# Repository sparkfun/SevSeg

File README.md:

This library allows an Arduino to easily display numbers and characters on a 4 digit 7-segment display without a separate 7-segment display controller.
It works for any digital pin arrangement, common anode and common cathode displays. It also has character support including letters A-F and many symbols. 

Hardware Setup
--------------
4 digit 7 segment displays use 12 digital pins. You may need more pins if your display has colons or apostrophes.

There are 4 digit pins and 8 segment pins. Digit pins are connected to the cathodes for common cathode displays, or anodes for common anode displays. 8 pins control the individual segments (seven segments plus the decimal point). 

Connect the four digit pins with four limiting resistors in series to any digital or analog pins. Connect the eight segment pins to any digital or analog pins (no limiting resistors needed). See the SevSeg example for more connection information.

Repository Contents
-------------------

* **/examples** - Arduino example sketches
* **/src** - Source files for Arduino library

Documentation
--------------
* **[Hookup Guide](https://learn.sparkfun.com/tutorials/using-the-serial-7-segment-display)** - Basic hookup guide for the Serial Segment Displays.
* **[Compatible Displays](https://www.sparkfun.com/wish_lists/120699)** - Products that work with this code. 

License Information
-------------------
Original Library by Dean Reading (deanreading@hotmail.com: http://arduino.cc/playground/Main/SevenSegmentLibrary), 2012

Improvements by Nathan Seidle, 2012

All code is open source so please feel free to do anything you want with it; you buy me a beer if you use this and we meet someday ([Beerware license](http://en.wikipedia.org/wiki/Beerware)).

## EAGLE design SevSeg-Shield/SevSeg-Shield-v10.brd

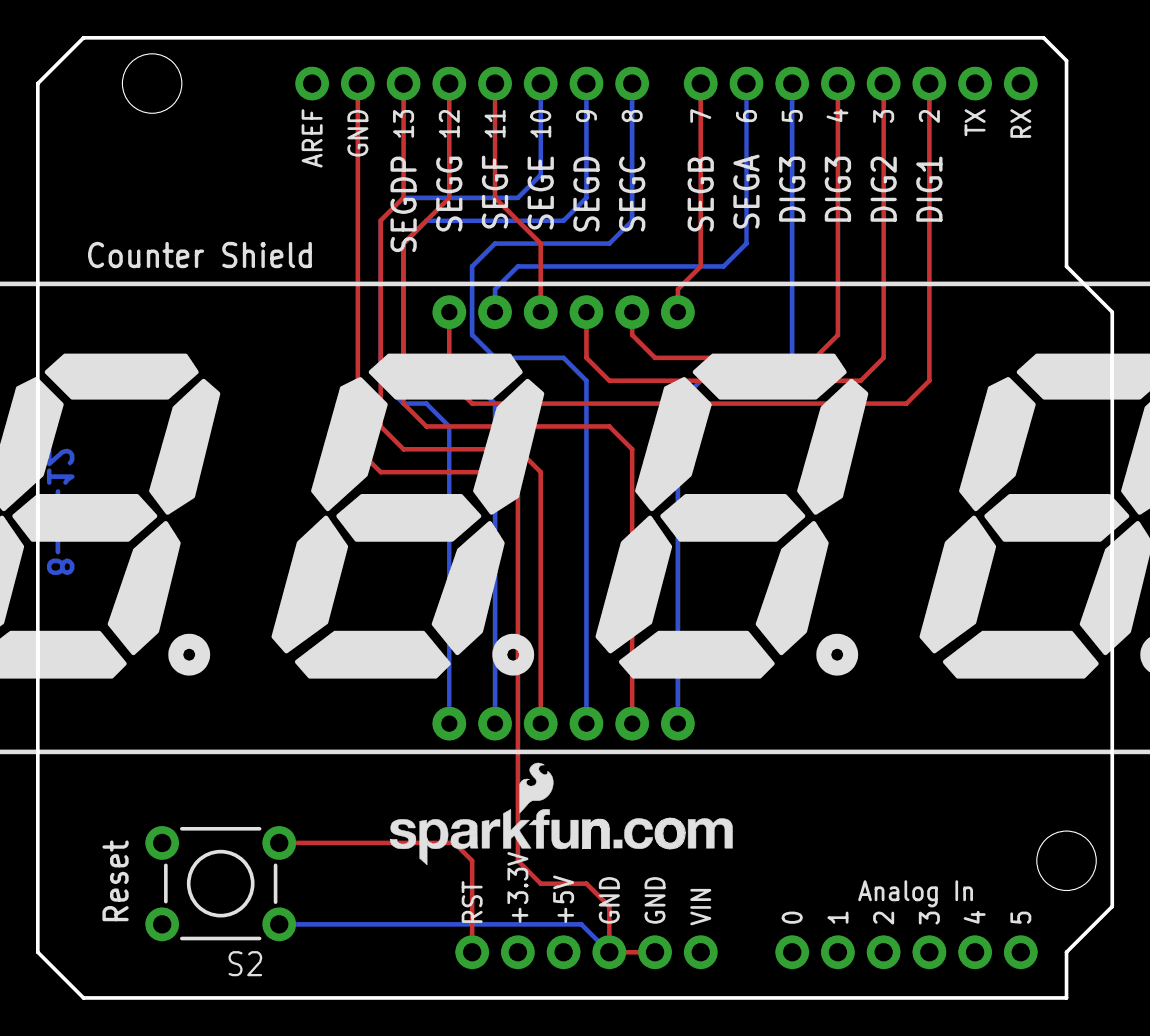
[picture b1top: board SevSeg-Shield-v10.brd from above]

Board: 2 copper layers, 59.7 x 53.3 mm, 5 parts (0 on the bottom side), 14 nets.

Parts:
S2: Reset; TACTILE-PTH
U2: ARDUINO_SHIELD; DUEMILANOVE_SHIELD
U$1: 7-SEGMENT-4DIGIT-COUNTERPTH; 7-SEGMENT-4DIGIT-COUNTER
U$3: CREATIVE_COMMONS
U$7: LOGO-SFENEW; SFE-NEW-WEBLOGO

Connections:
ARST: S2.3, U2.RES
DIG1: U2.D2, U$1.12
DIG2: U2.D3, U$1.9
DIG3: U2.D4, U$1.8
DIG4: U2.D5, U$1.6
GND: S2.1, U2.GND@0, U2.GND@1, U2.GND@2
SEGA: U2.D6, U$1.11
SEGB: U2.D7, U$1.7
SEGC: U2.D8, U$1.4
SEGD: U2.D9, U$1.2
SEGDP: U2.D13, U$1.3
SEGE: U2.D10, U$1.1
SEGF: U2.D11, U$1.10
SEGG: U2.D12, U$1.5

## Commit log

2012-07-24 Original commit. White space modifications to cpp before diving in.
    Added readme. Extended the 'counter' example.
2012-07-24 Re-wrote with lesson learned from BigTime. Runs faster with lesson code words now. Should be more read-able.
2012-08-03 Updates to library. Added example shield layout with 1" 4 digit display.
2012-09-23 Updated the footprint of the display.
    Proto worked but the footprint was not quite right. This version should
    work a lot better.
2012-10-21 Updated some basics in the example code. Nothing major.
    Basic comment corrections. But I am planning to add string support so
    that you can call "A123" and get letters and numbers displayed.
2012-10-21 Converted SevSeg library to work with strings instead of just numbers.
    DisplayNumber is now DisplayString. This allows us to print quite a few
    more characters on a 7-seg display instead of just numbers. It makes it
    a bit more difficult to print to the display (hint use sprintf) but it's
    more flexible. Example
2012-10-21 Updated readme.
2012-10-21 Removed unused functions from SevSeg.cpp. Updated readme.
2012-11-02 Added brightness control into the library.
    By setting a frame size of about 3000us, the library now varies the
    amount of time the display is on and off. This means you only need to
    call .DisplayString over and over again.
2012-11-02 Added a SetBrightness command. Now uses percentage 0 to 100.
    Error checking and correct mapping of the delay values are now
    calculated for the user in the SetBrightness command. User supplies
    value 0 to 100 percent and SetBrightness maps to correct delay value.
2012-11-02 Added support for Colon and Apostrophe
    Added another Begin() option, which includes four more parameters to
    define colon and apostrophe pins
    Also a big change to the way the decimal point(s) are displayed. Wanted
    the ability to display multiple at once.
2012-11-05 Adding support for colon and apostrophe.
    Jim had some great additions including a trick to support displays that
    don't have apos/colon. Because colons and apos are their own LEDs, I
    moved the apos/colon handling outside the main digit loop. I treat the
    apos/colon as LEDs rather than segments on a digit. This made it easier
    for me to understand what was/was not working.
2012-11-05 Incorporating Nathan's col/apostrophe support
2012-11-05 Support for individual segment control
    If a character-to-display is between 128-255 (the msb is set) the
    display goes into bit-per-segment mode. In this case, the lower 7 bits
    are each mapped to a segment.
    A change like this will be required to enable the [individual segment
    control](https://github.com/sparkfun/Serial7SegmentDisplay/wiki/Special-Commands#wiki-individual)
    command on the S7S.
2012-11-05 charToDisplay back to a char variable, comments
2012-11-22 Small changes to example counter sketch.
2012-11-25 reduce memory usage
2013-01-01 Reduced variable usage in .begin
    Removed two unneeded for loops. Also re-arranged pin setup so that we
    set the pin's state before we set the pinMode.
2013-04-18 Update repo structure and cleaned up README
2014-03-07 Adding support for the HP 7-Segment Bubble Display
    Added 3 example sketches that cover numbers, text, and using both to
    print sensor data to the bubble display.
2014-03-10 Fixed pin declaration comments to match pinout for bubble display
    Fixed pin declaration comments to match pinout for bubble display
2014-04-10 Update SevSeg.h
    Fixed 0b1101111, // 80 'P' to the correct 0b1100111, // 80 'P'
2015-03-11 Changing characterArray type from prog_uint8_t to uint8_t (required for Arduino 1.6 compatibility).
2015-04-24 Revising structure to match 1.6 standard.
2015-06-14 Fixes decimal point in example and improves the examples
    * Default example shows no decimal point although the comment mentions
    one, fix it and adds one at the third position
    * Adds a hint to the usage of decimal point argument (binary number)
    * Improves the other examples for more variety
2015-12-03 Update README.md
    Adding documentation links.
2016-09-30 Include 7-segment map in comment.
2016-09-30 More faithfull representation of the character displayed on the LCD.
2016-09-30 Nicer characterArray comments.
    Align columns.
2016-09-30 Nicer characterArray comments.
    Streamline format (add first numeric characters).
2016-09-30 Remove unecessary comment.
2016-09-30 Remove segment map (better one available below).
2016-09-30 Factorize PROGMEM reads in a local var.
2017-02-07 DisplayString() using no delays
    The DisplayString function has been updated to eliminate any delay.
    Rather than iterating through the digits in a for loop every time the
    function is called, this approach iterates on a static variable only
    after a given time has elapsed regardless of how often the function is
    called. In order to get this working while preserving all other
    functionality (brightness, different numbers/types of digits, etc.) the
2017-02-11 fixed decimal point
    previous update caused the decimal point to stop working.
2017-02-13 Incremented verion number for Arduino library
2017-02-13 Changed type of characterToDisplay to unsigned since it's used to index an array
2017-02-13 Made c string parameter const to allow passing of string literal w/o warnings. Removed trailing whitespace
2018-05-13 added 'a'
    sometimes a lower case 'a' looks better

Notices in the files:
parts and their libraries:
SparkFun: Released under the Creative Commons Attribution Share-Alike 3.0 License
SparkFun: http://creativecommons.org/licenses/by-sa/3.0
SparkFun-Displays: Licensing: CC v3.0 Share-Alike You are welcome to use this library for commercial purposes.
